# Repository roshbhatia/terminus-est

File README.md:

# terminus-est

> Resolution and a plan are better than a sword, because a man whets his own edges on them.
> > Gene Wolfe - The Citadel of the Autarch

---

## Background
Terminus Est is a ergonomic (but somewhat conventional) split keyboard tuned to my developer workflow.
I've tended to cluster my actions around vim-inpsired keybindings with discrete "leader" keys, and started to wish that my leader keys were a bit easier to hit.
Rather than using stabilizers with longer keys, I've decided to use multiple 1U keys in some places, mostly for aesthetics. However, the keymapping may change in the future.

This project was frustratingly complicated, too expensive, and ultimately worse than my perfectly fine, working keyboards. But it's worth it to build something cool.

Thanks to @dededecline for the great advice and @kh3dron for making the plate look nice when I couldn't figure out the CAD stuff.

---

## Gallery

<details open>
<summary>PCB</summary>

### Front

### Back

### Traces

</details>

<details open>
<summary>Layout</summary>

</details>

<details open>
<summary>Plate</summary>

</details>

<details open>
<summary>Case</summary>

</details>

---

## Pinout

```mermaid
graph LR
    subgraph Columns["Columns"]
        COL0["COL0"]
        COL1["COL1"]
        COL2["COL2"]
        COL3["COL3"]
        COL4["COL4"]
        COL5["COL5"]
        COL6["COL6"]
        COL7["COL7"]
        COL8["COL8"]
        COL9["COL9"]
        COL12["COL12"]
        COL13["COL13"]
        COL14["COL14"]
        COL15["COL15"]
        COL16["COL16"]
        COL17["COL17"]
        COL18["COL18"]
        COL19["COL19"]
        COL20["COL20"]
        COL21["COL21"]
    end

    subgraph RPi["Raspberry Pi Pico"]
        GP0["GP0"]
        GP1["GP1"]
        GP2["GP2"]
        GP3["GP3"]
        GP4["GP4"]
        GP5["GP5"]
        GP6["GP6"]
        GP7["GP7"]
        GP8["GP8"]
        GP9["GP9"]
        GP10["GP10"]
        GP11["GP11"]
        GP12["GP12"]
        GP13["GP13"]
        GP14["GP14"]
        GP15["GP15"]
        GP16["GP16"]
        GP17["GP17"]
        GP18["GP18"]
        GP19["GP19"]
        GP20["GP20"]
        GP21["GP21"]
        GP22["GP22"]
        GP26["GP26"]
        GP27["GP27"]
        GP28["GP28"]
    end

    subgraph Rows["Rows"]
        ROW0["ROW0"]
        ROW1["ROW1"]
        ROW2["ROW2"]
        ROW3["ROW3"]
        ROW4["ROW4"]
        ROW5["ROW5"]
    end

    GP0 --> COL0
    GP1 --> COL1
    GP2 --> COL2
    GP3 --> COL3
    GP4 --> COL4
    GP5 --> COL5
    GP6 --> COL6
    GP7 --> COL7
    GP8 --> COL8
    GP9 --> COL9
    GP16 --> COL12
    GP17 --> COL13
    GP18 --> COL14
    GP19 --> COL15
    GP20 --> COL16
    GP21 --> COL17
    GP22 --> COL18
    GP26 --> COL19
    GP27 --> COL20
    GP28 --> COL21

    GP10 --> ROW0
    GP11 --> ROW1
    GP12 --> ROW2
    GP13 --> ROW3
    GP14 --> ROW4
    GP15 --> ROW5
```

---

## Built With

- [Raspberry Pi Pico](https://www.raspberrypi.com/products/raspberry-pi-pico/)
- [KLE (Keyboard Layout Editor)](http://www.keyboard-layout-editor.com/)
- [KiCad](https://www.kicad.org/)
- [Fusion 360](https://www.autodesk.com/products/fusion-360/)
- [keyboard-tools.xyz](https://keyboard-tools.xyz/)
- [kbplate (ai03)](https://kbplate.ai03.com/)
- [KMK Firmware](https://github.com/KMKfw/kmk_firmware)
- [OpenSCAD](https://openscad.org/)

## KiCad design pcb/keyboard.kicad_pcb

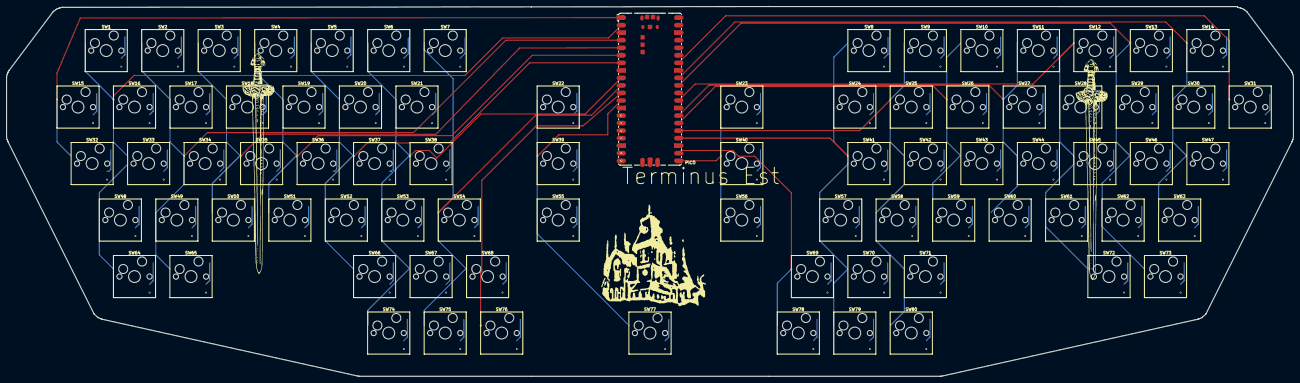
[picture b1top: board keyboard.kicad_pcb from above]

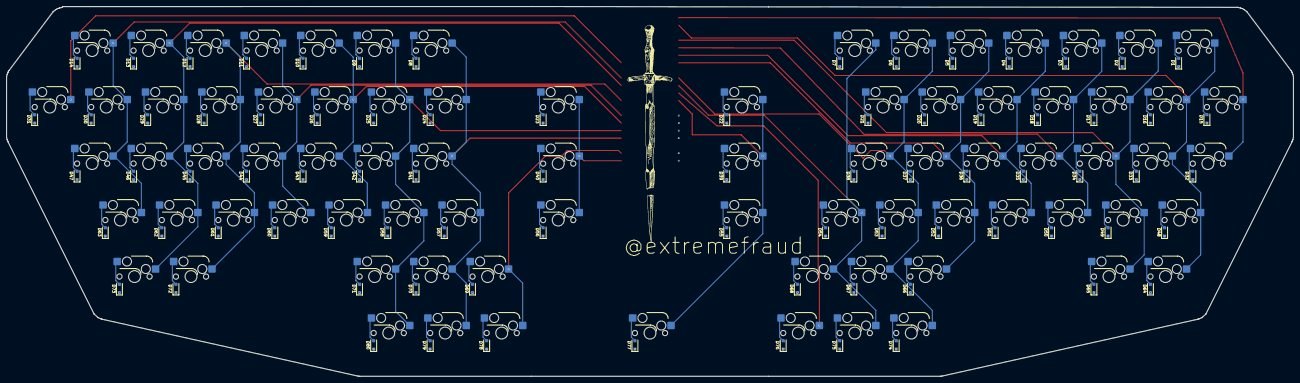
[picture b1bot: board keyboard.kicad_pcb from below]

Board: 4 copper layers, 434.0 x 124.7 mm, 161 parts (80 on the bottom side), 106 nets.

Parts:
D1, D2, D3, D4, D5, D6, D7, D8, D9, D10, D11, D12, D13, D14, D15, D16, D17, D18, D19, D20, D21, D22, D23, D24, D25, D26, D27, D28, D29, D30, D31, D32, D33, D34, D35, D36, D37, D38, D39, D40, D41, D42, D43, D44, D45, D46, D47, D48, D49, D50, D51, D52, D53, D54, D55, D56, D57, D58, D59, D60, D61, D62, D63, D64, D65, D66, D67, D68, D69, D70, D71, D72, D73, D74, D75, D76, D77, D78, D79, D80: D; D_SOD-123F
PICO: RaspberryPi_Pico_SMD
SW1, SW2, SW3, SW4, SW5, SW6, SW7, SW8, SW9, SW10, SW11, SW12, SW13, SW14, SW15, SW16, SW17, SW18, SW19, SW20, SW21, SW22, SW23, SW24, SW25, SW26, SW27, SW28, SW29, SW30, SW31, SW32, SW33, SW34, SW35, SW36, SW37, SW38, SW39, SW40, SW41, SW42, SW43, SW44, SW45, SW46, SW47, SW48, SW49, SW50, SW51, SW52, SW53, SW54, SW55, SW56, SW57, SW58, SW59, SW60, SW61, SW62, SW63, SW64, SW65, SW66, SW67, SW68, SW69, SW70, SW71, SW72, SW73, SW74, SW75, SW76, SW77, SW78, SW79, SW80: SW_Push; SW_Hotswap_Kailh_MX_1.00u

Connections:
COL0: PICO.1, SW15.1, SW32.1
COL1: PICO.2, SW1.1, SW16.1, SW33.1, SW48.1, SW64.1
COL2: PICO.4, SW2.1, SW17.1, SW34.1, SW49.1, SW65.1
COL3: PICO.5, SW3.1, SW18.1, SW35.1, SW50.1
COL4: PICO.6, SW4.1, SW19.1, SW36.1, SW51.1
COL5: PICO.7, SW5.1, SW20.1, SW37.1, SW52.1, SW66.1
COL6: PICO.9, SW6.1, SW21.1, SW38.1, SW53.1, SW67.1, SW74.1
COL7: PICO.10, SW7.1, SW54.1, SW68.1, SW75.1
COL8: PICO.11, SW76.1
COL9: PICO.12, SW22.1, SW39.1, SW55.1, SW77.1
COL12: PICO.21, SW23.1, SW40.1, SW56.1
COL13: PICO.22, SW69.1, SW78.1
COL14: PICO.24, SW8.1, SW24.1, SW41.1, SW57.1, SW70.1, SW79.1
COL15: PICO.25, SW9.1, SW25.1, SW42.1, SW58.1, SW71.1, SW80.1
COL16: PICO.26, SW10.1, SW26.1, SW43.1, SW59.1
COL17: PICO.27, SW11.1, SW27.1, SW44.1, SW60.1
COL18: PICO.29, SW12.1, SW28.1, SW45.1, SW61.1, SW72.1
COL19: PICO.31, SW13.1, SW29.1, SW46.1, SW62.1, SW73.1
COL20: PICO.32, SW14.1, SW30.1, SW47.1, SW63.1
COL21: PICO.34, SW31.1
unnamed: D1.2, SW1.2
unnamed: D2.2, SW2.2
unnamed: D3.2, SW3.2
unnamed: D4.2, SW4.2
unnamed: D5.2, SW5.2
unnamed: D6.2, SW6.2
unnamed: D7.2, SW7.2
unnamed: D8.2, SW8.2
unnamed: D9.2, SW9.2
unnamed: D10.2, SW10.2
unnamed: D11.2, SW11.2
unnamed: D12.2, SW12.2
unnamed: D13.2, SW13.2
unnamed: D14.2, SW14.2
unnamed: D15.2, SW15.2
unnamed: D16.2, SW16.2
unnamed: D17.2, SW17.2
unnamed: D18.2, SW18.2
unnamed: D19.2, SW19.2
unnamed: D20.2, SW20.2
unnamed: D21.2, SW21.2
unnamed: D22.2, SW22.2
unnamed: D23.2, SW23.2
unnamed: D24.2, SW24.2
unnamed: D25.2, SW25.2
unnamed: D26.2, SW26.2
unnamed: D27.2, SW27.2
unnamed: D28.2, SW28.2
unnamed: D29.2, SW29.2
unnamed: D30.2, SW30.2
unnamed: D31.2, SW31.2
unnamed: D32.2, SW32.2
unnamed: D33.2, SW33.2
unnamed: D34.2, SW34.2
unnamed: D35.2, SW35.2
unnamed: D36.2, SW36.2
unnamed: D37.2, SW37.2
unnamed: D38.2, SW38.2
unnamed: D39.2, SW39.2
unnamed: D40.2, SW40.2
unnamed: D41.2, SW41.2
unnamed: D42.2, SW42.2
unnamed: D43.2, SW43.2
unnamed: D44.2, SW44.2
unnamed: D45.2, SW45.2
unnamed: D46.2, SW46.2
unnamed: D47.2, SW47.2
unnamed: D48.2, SW48.2
unnamed: D49.2, SW49.2
unnamed: D50.2, SW50.2
unnamed: D51.2, SW51.2
unnamed: D52.2, SW52.2
unnamed: D53.2, SW53.2
unnamed: D54.2, SW54.2
unnamed: D55.2, SW55.2
unnamed: D56.2, SW56.2
unnamed: D57.2, SW57.2
unnamed: D58.2, SW58.2
unnamed: D59.2, SW59.2
unnamed: D60.2, SW60.2
unnamed: D61.2, SW61.2
unnamed: D62.2, SW62.2
unnamed: D63.2, SW63.2
unnamed: D64.2, SW64.2
unnamed: D65.2, SW65.2
unnamed: D66.2, SW66.2
unnamed: D67.2, SW67.2
unnamed: D68.2, SW68.2
unnamed: D69.2, SW69.2
unnamed: D70.2, SW70.2
unnamed: D71.2, SW71.2
unnamed: D72.2, SW72.2
unnamed: D73.2, SW73.2
unnamed: D74.2, SW74.2
unnamed: D75.2, SW75.2
unnamed: D76.2, SW76.2
unnamed: D77.2, SW77.2
unnamed: D78.2, SW78.2
unnamed: D79.2, SW79.2
unnamed: D80.2, SW80.2
ROW0: D1.1, D2.1, D3.1, D4.1, D5.1, D6.1, D7.1, D8.1, D9.1, D10.1, D11.1, D12.1, D13.1, D14.1, PICO.14
ROW1: D15.1, D16.1, D17.1, D18.1, D19.1, D20.1, D21.1, D22.1, D23.1, D24.1, D25.1, D26.1, D27.1, D28.1, D29.1, D30.1, D31.1, PICO.15
ROW2: D32.1, D33.1, D34.1, D35.1, D36.1, D37.1, D38.1, D39.1, D40.1, D41.1, D42.1, D43.1, D44.1, D45.1, D46.1, D47.1, PICO.16
ROW3: D48.1, D49.1, D50.1, D51.1, D52.1, D53.1, D54.1, D55.1, D56.1, D57.1, D58.1, D59.1, D60.1, D61.1, D62.1, D63.1, PICO.17
ROW4: D64.1, D65.1, D66.1, D67.1, D68.1, D69.1, D70.1, D71.1, D72.1, D73.1, PICO.19
ROW5: D74.1, D75.1, D76.1, D77.1, D78.1, D79.1, D80.1, PICO.20

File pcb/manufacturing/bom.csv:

Designator,Footprint,Quantity,Value,LCSC Part #
"D1, D10, D11, D12, D13, D14, D15, D16, D17, D18, D19, D2, D20, D21, D22, D23, D24, D25, D26, D27, D28, D29, D3, D30, D31, D32, D33, D34, D35, D36, D37, D38, D39, D4, D40, D41, D42, D43, D44, D45, D46, D47, D48, D49, D5, D50, D51, D52, D53, D54, D55, D56, D57, D58, D59, D6, D60, D61, D62, D63, D64, D65, D66, D67, D68, D69, D7, D70, D71, D72, D73, D74, D75, D76, D77, D78, D79, D8, D80, D9",D_SOD-123F,80,D,C22374920
PICO,RaspberryPi_Pico_SMD,1,RaspberryPi_Pico_SMD,C7203002
"SW1, SW10, SW11, SW12, SW13, SW14, SW15, SW16, SW17, SW18, SW19, SW2, SW20, SW21, SW22, SW23, SW24, SW25, SW26, SW27, SW28, SW29, SW3, SW30, SW31, SW32, SW33, SW34, SW35, SW36, SW37, SW38, SW39, SW4, SW40, SW41, SW42, SW43, SW44, SW45, SW46, SW47, SW48, SW49, SW5, SW50, SW51, SW52, SW53, SW54, SW55, SW56, SW57, SW58, SW59, SW6, SW60, SW61, SW62, SW63, SW64, SW65, SW66, SW67, SW68, SW69, SW7, SW70, SW71, SW72, SW73, SW74, SW75, SW76, SW77, SW78, SW79, SW8, SW80, SW9",SW_Hotswap_Kailh_MX_1.00u,80,SW_Push,C49352235

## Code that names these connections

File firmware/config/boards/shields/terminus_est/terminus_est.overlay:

/*
 * Copyright (c) 2024 The ZMK Contributors
 *
 * SPDX-License-Identifier: MIT
 */

#include "terminus_est.dtsi"

&kscan0 {
	col-gpios
		= <&pro_micro 0 GPIO_ACTIVE_HIGH>   // COL0  (GP0)
		, <&pro_micro 1 GPIO_ACTIVE_HIGH>   // COL1  (GP1)
		, <&pro_micro 2 GPIO_ACTIVE_HIGH>   // COL2  (GP2)
		, <&pro_micro 3 GPIO_ACTIVE_HIGH>   // COL3  (GP3)
		, <&pro_micro 4 GPIO_ACTIVE_HIGH>   // COL4  (GP4)
		, <&pro_micro 5 GPIO_ACTIVE_HIGH>   // COL5  (GP5)
		, <&pro_micro 6 GPIO_ACTIVE_HIGH>   // COL6  (GP6)
		, <&pro_micro 7 GPIO_ACTIVE_HIGH>   // COL7  (GP7)
		, <&pro_micro 8 GPIO_ACTIVE_HIGH>   // COL8  (GP8)
		, <&pro_micro 9 GPIO_ACTIVE_HIGH>   // COL9  (GP9)
		, <&pro_micro 16 GPIO_ACTIVE_HIGH>  // COL10 (GP16)
		, <&pro_micro 17 GPIO_ACTIVE_HIGH>  // COL11 (GP17)
		, <&pro_micro 18 GPIO_ACTIVE_HIGH>  // COL12 (GP18)
		, <&pro_micro 19 GPIO_ACTIVE_HIGH>  // COL13 (GP19)
		, <&pro_micro 20 GPIO_ACTIVE_HIGH>  // COL14 (GP20)
		, <&pro_micro 21 GPIO_ACTIVE_HIGH>  // COL15 (GP21)
		, <&pro_micro 22 GPIO_ACTIVE_HIGH>  // COL16 (GP22)
		, <&pro_micro 26 GPIO_ACTIVE_HIGH>  // COL17 (GP26)
		, <&pro_micro 27 GPIO_ACTIVE_HIGH>  // COL18 (GP27)
		, <&pro_micro 28 GPIO_ACTIVE_HIGH>  // COL19 (GP28)
		;
};

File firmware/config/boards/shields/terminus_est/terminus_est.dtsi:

/*
 * Copyright (c) 2024 The ZMK Contributors
 *
 * SPDX-License-Identifier: MIT
 */

#include <dt-bindings/zmk/matrix_transform.h>
#include "terminus_est-layouts.dtsi"

/ {
	chosen {
		zmk,kscan = &kscan0;
		zmk,physical_layout = &physical_layout0;
	};

	default_transform: keymap_transform_0 {
		compatible = "zmk,matrix-transform";
		columns = <20>;
		rows = <6>;

		map = <
RC(0,1) RC(0,2) RC(0,3) RC(0,4) RC(0,5) RC(0,6) RC(0,7)                                     RC(0,12) RC(0,13) RC(0,14) RC(0,15) RC(0,16) RC(0,17) RC(0,18)
RC(1,0) RC(1,1) RC(1,2) RC(1,3) RC(1,4) RC(1,5) RC(1,6)             RC(1,9)                         RC(1,10) RC(1,12) RC(1,13) RC(1,14) RC(1,15) RC(1,16) RC(1,17) RC(1,18) RC(1,19)
RC(2,0) RC(2,1) RC(2,2) RC(2,3) RC(2,4) RC(2,5) RC(2,6)             RC(2,9)                         RC(2,10) RC(2,12) RC(2,13) RC(2,14) RC(2,15) RC(2,16) RC(2,17) RC(2,18)
        RC(3,1) RC(3,2) RC(3,3) RC(3,4) RC(3,5) RC(3,6) RC(3,7)     RC(3,9)                         RC(3,10) RC(3,12) RC(3,13) RC(3,14) RC(3,15) RC(3,16) RC(3,17) RC(3,18)
        RC(4,1) RC(4,2)         RC(4,5) RC(4,6) RC(4,7)                                     RC(4,11) RC(4,12) RC(4,13)         RC(4,16) RC(4,17)
                                        RC(5,6) RC(5,7) RC(5,8) RC(5,9)             RC(5,11) RC(5,12) RC(5,13)
		>;
	};

	kscan0: kscan {
		compatible = "zmk,kscan-gpio-matrix";

		diode-direction = "col2row";
		row-gpios
			= <&pro_micro 10 (GPIO_ACTIVE_HIGH | GPIO_PULL_DOWN)>   // ROW0 (GP10)
			, <&pro_micro 11 (GPIO_ACTIVE_HIGH | GPIO_PULL_DOWN)>   // ROW1 (GP11)
			, <&pro_micro 12 (GPIO_ACTIVE_HIGH | GPIO_PULL_DOWN)>   // ROW2 (GP12)
			, <&pro_micro 13 (GPIO_ACTIVE_HIGH | GPIO_PULL_DOWN)>   // ROW3 (GP13)
			, <&pro_micro 14 (GPIO_ACTIVE_HIGH | GPIO_PULL_DOWN)>   // ROW4 (GP14)
			, <&pro_micro 15 (GPIO_ACTIVE_HIGH | GPIO_PULL_DOWN)>   // ROW5 (GP15)
			;
	};
};

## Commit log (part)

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2025-09-18 add initial keyboard layout
2025-09-18 make layout more ergonomic
2025-09-18 adds layout image
2025-09-18 adds firmware for current layout
2025-09-18 add initial readme
2025-09-19 we do it big
2025-09-19 fix layout mistakes
2025-09-19 more layout improvements (final?) and remove firmware until we ship pcb
2025-09-19 ok last layout
2025-09-19 final final layout seriously no changes dude
2025-09-19 initial pcb commit
2025-09-20 alright alright. really last
2025-09-22 wider
2025-09-22 regen keyboard
2025-09-23 finished routing
2025-09-23 page settings
2025-09-24 graphics
2025-09-27 add qmk firmware
2025-09-27 add shell nix
2025-09-27 remove qmk directly
2025-09-28 boostrap firmware
2025-09-28 migrate to stuff
2025-09-29 migrate from qmk to zmk
2025-09-29 regen production files
2025-09-30 pugh
2025-09-30 fixup firmware
2025-09-30 fixup firmware tests
2025-09-30 do it the right way with QMK
2025-09-30 qmk stuff
2025-10-01 remove firmware
2025-10-02 cleanup targets
2025-10-02 add case info
2025-10-05 revamp readme
2025-10-17 add openscad plate gen
